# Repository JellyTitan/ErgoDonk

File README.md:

# ErgoDonk v0.9
ErgoDox variant that uses standard 100% SA keycaps, Blackpill MCU and an FDM printed case. 

[keyboard layout editor](http://www.keyboard-layout-editor.com/#/gists/ac776db3b0deef94de51943c384cfdfc)

## Build Log
Experiments to date:
* Prototype initially built with Blackpill MCU. Works well.
* Refactored to use LED
* Refactored to use ProMicro
* Refactored to use Pico 2040
* Prototype sent out for production 7-26-2023

### Lessons learned from the ds simple prototype (todo)
* Fix the stabilizers. Two screw-in PCB stabalizers won't fit next to each other on the thumb cluster - try the plate mount stabs instead.

* Take a closer look at routing by the rotary encoders - may be a short
* The DS version is charged as two keyboards by JLCPCB - compare pricing for building as two seperate halves.
* The RH Trackball has 2 separate pcbs. Top one sent out for prototype, bottom needs to be made.

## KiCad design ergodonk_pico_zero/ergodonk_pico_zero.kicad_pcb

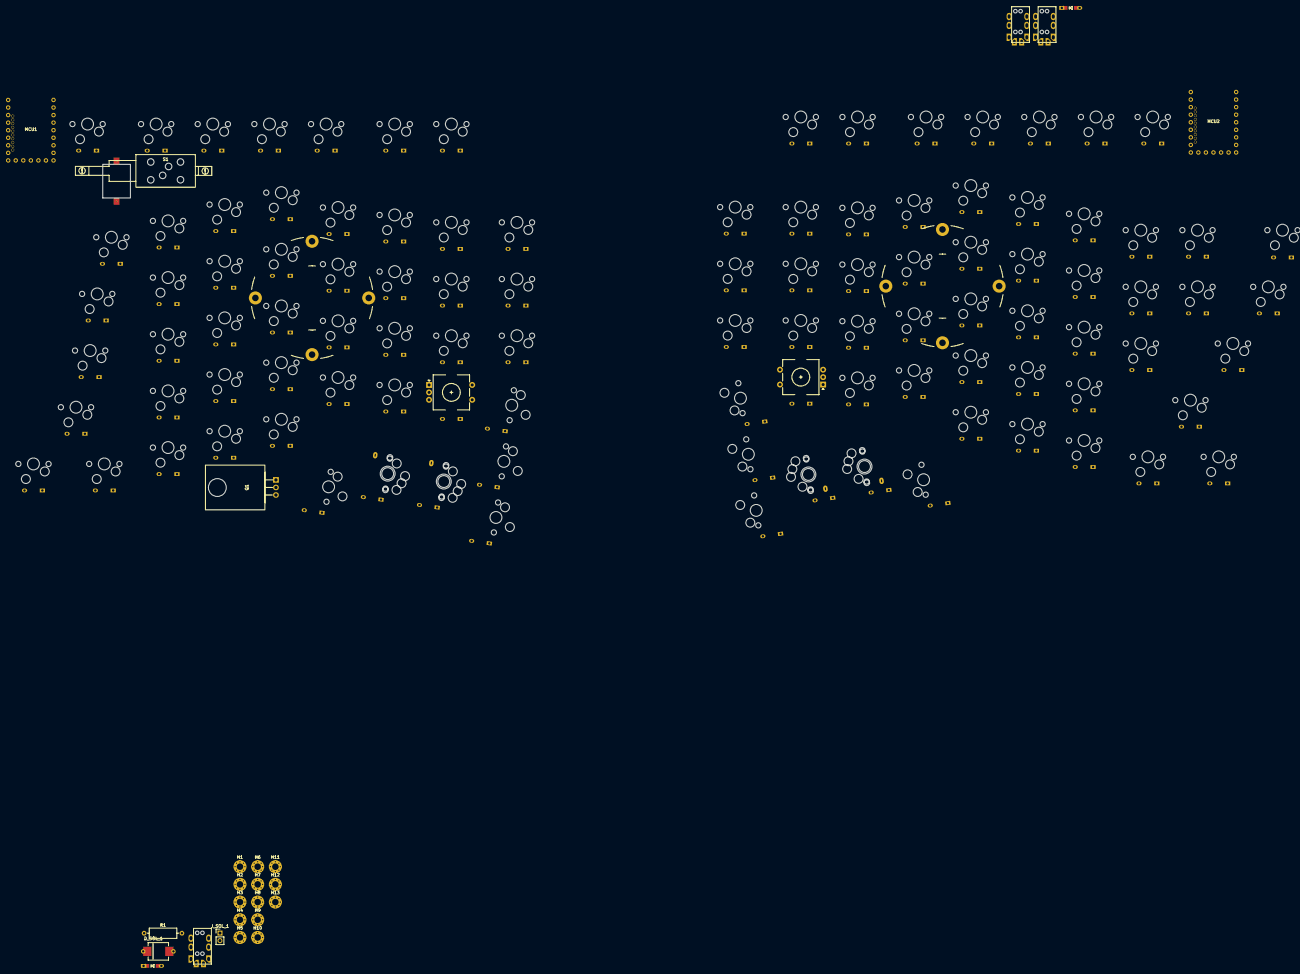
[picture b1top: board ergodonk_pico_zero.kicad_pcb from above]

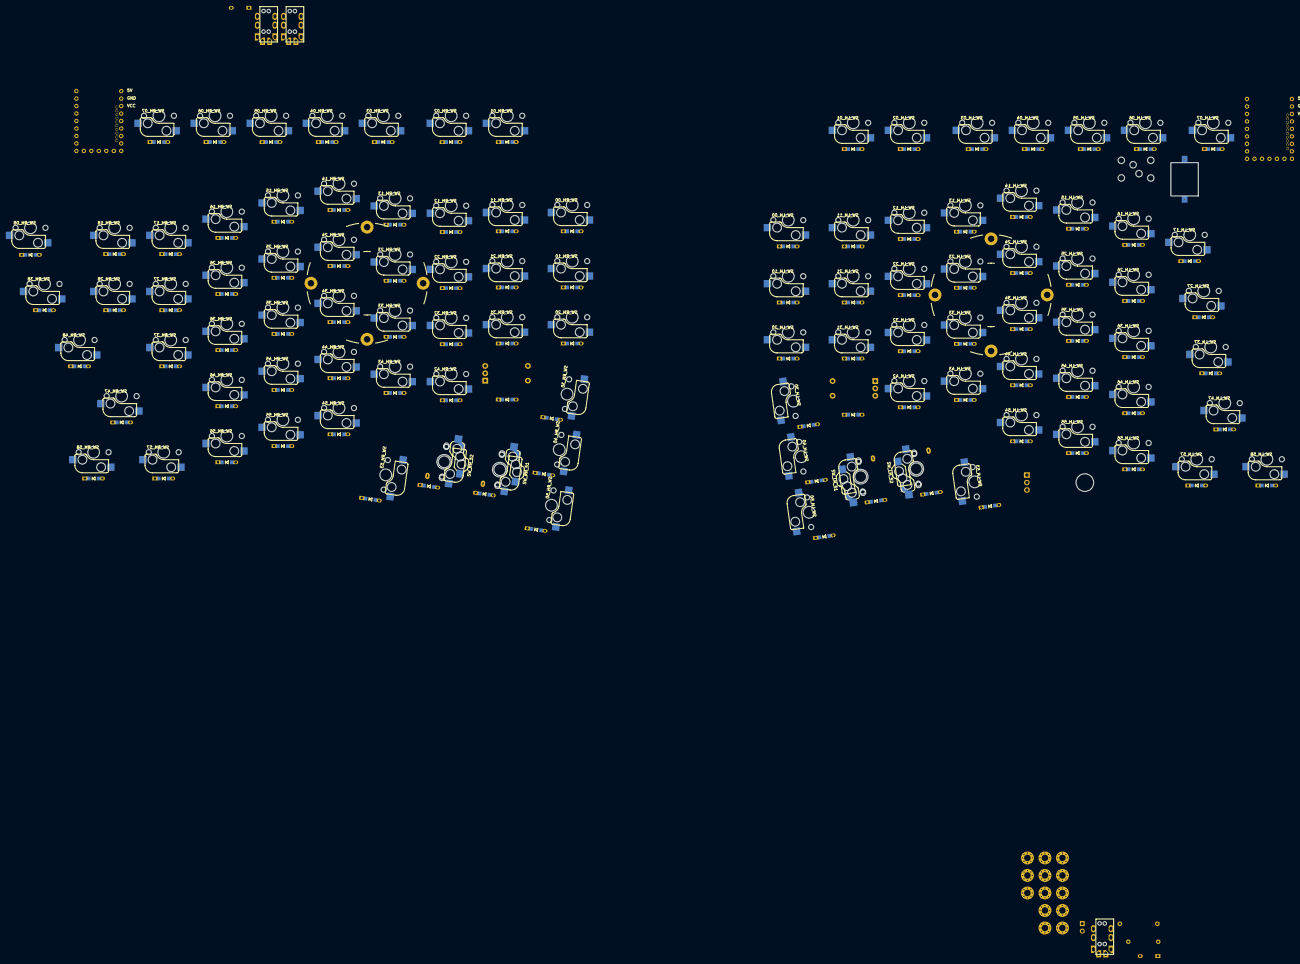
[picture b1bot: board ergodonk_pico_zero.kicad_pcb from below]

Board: 2 copper layers, 234 parts (204 on the bottom side), 143 nets, no tracks yet.

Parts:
D1, D102: D; D3_TH_SMD_v2
D_LH_00, D_LH_01, D_LH_02, D_LH_03, D_LH_04, D_LH_05, D_LH_06, D_LH_07, D_LH_10, D_LH_11, D_LH_12, D_LH_13, D_LH_14, D_LH_15, D_LH_16, D_LH_17, D_LH_20, D_LH_21, D_LH_22, D_LH_23, D_LH_24, D_LH_25, D_LH_26, D_LH_27, D_LH_30, D_LH_31, D_LH_32, D_LH_33, D_LH_34, D_LH_35, D_LH_36, D_LH_37, D_LH_40, D_LH_41, D_LH_42, D_LH_43, D_LH_44, D_LH_45, D_LH_46, D_LH_47, D_LH_50, D_LH_51, D_LH_52, D_LH_53, D_LH_54, D_LH_55, D_LH_56, D_LH_57, D_LH_58: D; D3_TH_SMD_v2
D_RH_00, D_RH_01, D_RH_02, D_RH_03, D_RH_04, D_RH_05, D_RH_06, D_RH_07, D_RH_08, D_RH_10, D_RH_11, D_RH_12, D_RH_13, D_RH_14, D_RH_15, D_RH_16, D_RH_17, D_RH_18, D_RH_20, D_RH_21, D_RH_22, D_RH_23, D_RH_24, D_RH_25, D_RH_26, D_RH_27, D_RH_28, D_RH_30, D_RH_31, D_RH_32, D_RH_33, D_RH_34, D_RH_35, D_RH_36, D_RH_37, D_RH_38, D_RH_40, D_RH_41, D_RH_42, D_RH_43, D_RH_44, D_RH_45, D_RH_46, D_RH_47, D_RH_48, D_RH_50, D_RH_51, D_RH_52, D_RH_53, D_RH_54, D_RH_55, D_RH_56, D_RH_57, D_RH_58: D; D3_TH_SMD_v2
D_SOL_1: MUR340S; MUR340S_IN4001_TH_HYBRID
H1, H2, H3, H4, H5, H6, H7, H8, H9, H10, H11, H12, H13: MountingHole; MountingHole_2.2mm_M2_Pad_Via
H14, H15: Tenting puck mount; Tenting_Puck.kicad_mod_nocenter
J1, J3, J4: AudioJack4; MJ-4PP-9_CANTOR_KITCHEN_SINK
J_SOL_1: Conn_01x02_Female; PinHeader_1x02_P2.54mm_Vertical
LS1: AST1109MLTRQ_MAL; AST1109MLTRQ
MCU1, MCU2: rp2040-zero; rp2040 Zero DS
Q1: TIP120; Tip 120 with heatsink
R1: 1k; R_Axial_DIN0309_L9.0mm_D3.2mm_P12.70mm_Horizontal
S1: Solenoid; uxcell a14092600ux0438 solenoid
SWLH_ROT1: RotaryEncoder_Switch; RotaryEncoder_EC11_ergodonk_variant
SWRH_ROT1: RotaryEncoder_Switch; RotaryEncoder_EC11_ergodonk_variant
SW_LH_00, SW_LH_01, SW_LH_02, SW_LH_03, SW_LH_04, SW_LH_05, SW_LH_06, SW_LH_07, SW_LH_10, SW_LH_11, SW_LH_12, SW_LH_13, SW_LH_14, SW_LH_15, SW_LH_16, SW_LH_17, SW_LH_20, SW_LH_21, SW_LH_22, SW_LH_23, SW_LH_24, SW_LH_25, SW_LH_26, SW_LH_27, SW_LH_30, SW_LH_31, SW_LH_32, SW_LH_33, SW_LH_34, SW_LH_35, SW_LH_36, SW_LH_37, SW_LH_40, SW_LH_42, SW_LH_43, SW_LH_44, SW_LH_45, SW_LH_46, SW_LH_47, SW_LH_50, SW_LH_53, SW_LH_54, SW_LH_55, SW_LH_56, SW_LH_57, SW_LH_58: SW_PUSH; V2_CherryMX_Hotswap
SW_LH_51, SW_LH_52: SW_PUSH; V2_CherryMX_KailhV2_Hotswap
SW_RH_00, SW_RH_01, SW_RH_02, SW_RH_03, SW_RH_04, SW_RH_05, SW_RH_06, SW_RH_07, SW_RH_08, SW_RH_10, SW_RH_11, SW_RH_12, SW_RH_13, SW_RH_14, SW_RH_15, SW_RH_16, SW_RH_17, SW_RH_18, SW_RH_20, SW_RH_21, SW_RH_22, SW_RH_23, SW_RH_24, SW_RH_25, SW_RH_26, SW_RH_27, SW_RH_28, SW_RH_30, SW_RH_31, SW_RH_32, SW_RH_33, SW_RH_34, SW_RH_35, SW_RH_36, SW_RH_37, SW_RH_38, SW_RH_40, SW_RH_42, SW_RH_43, SW_RH_44, SW_RH_45, SW_RH_46, SW_RH_47, SW_RH_48, SW_RH_50, SW_RH_53, SW_RH_54, SW_RH_55, SW_RH_56, SW_RH_57, SW_RH_58: SW_PUSH; V2_CherryMX_Hotswap
SW_RH_51, SW_RH_52: SW_PUSH; V2_CherryMX_KailhV2_Hotswap

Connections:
+5V: MCU1.23 (5V), MCU2.23 (5V)
GND: LS1.2, MCU1.22 (GND), MCU2.22 (GND), Q1.3 (E), SWLH_ROT1.C, SWRH_ROT1.C
unnamed: D_LH_00.2 (A), SW_LH_00.2
unnamed: D_LH_01.2 (A), SW_LH_01.2
unnamed: D_LH_02.2 (A), SW_LH_02.2
unnamed: D_LH_03.2 (A), SW_LH_03.2
unnamed: D_LH_04.2 (A), SW_LH_04.2
unnamed: D_LH_05.2 (A), SW_LH_05.2
unnamed: D_LH_06.2 (A), SW_LH_06.2
unnamed: D_LH_07.2 (A), SW_LH_07.2
unnamed: D_LH_10.2 (A), SW_LH_10.2
unnamed: D_LH_11.2 (A), SW_LH_11.2
unnamed: D_LH_12.2 (A), SW_LH_12.2
unnamed: D_LH_13.2 (A), SW_LH_13.2
unnamed: D_LH_14.2 (A), SW_LH_14.2
unnamed: D_LH_15.2 (A), SW_LH_15.2
unnamed: D_LH_16.2 (A), SW_LH_16.2
unnamed: D_LH_17.2 (A), SW_LH_17.2
unnamed: D_LH_20.2 (A), SW_LH_20.2
unnamed: D_LH_21.2 (A), SW_LH_21.2
unnamed: D_LH_22.2 (A), SW_LH_22.2
unnamed: D_LH_23.2 (A), SW_LH_23.2
unnamed: D_LH_24.2 (A), SW_LH_24.2
unnamed: D_LH_25.2 (A), SW_LH_25.2
unnamed: D_LH_26.2 (A), SW_LH_26.2
unnamed: D_LH_27.2 (A), SW_LH_27.2
unnamed: D_LH_30.2 (A), SW_LH_30.2
unnamed: D_LH_31.2 (A), SW_LH_31.2
unnamed: D_LH_32.2 (A), SW_LH_32.2
unnamed: D_LH_33.2 (A), SW_LH_33.2
unnamed: D_LH_34.2 (A), SW_LH_34.2
unnamed: D_LH_35.2 (A), SW_LH_35.2
unnamed: D_LH_36.2 (A), SW_LH_36.2
unnamed: D_LH_37.2 (A), SW_LH_37.2
unnamed: D_LH_40.2 (A), SW_LH_40.2
unnamed: D_LH_42.2 (A), SW_LH_42.2
unnamed: D_LH_43.2 (A), SW_LH_43.2
unnamed: D_LH_44.2 (A), SW_LH_44.2
unnamed: D_LH_45.2 (A), SW_LH_45.2
unnamed: D_LH_46.2 (A), SW_LH_46.2
unnamed: D_LH_47.2 (A), SW_LH_47.2
unnamed: D_LH_50.2 (A), SW_LH_50.2
unnamed: D_LH_51.2 (A), SW_LH_51.2
unnamed: D_LH_52.2 (A), SW_LH_52.2
unnamed: D_LH_53.2 (A), SW_LH_53.2
unnamed: D_LH_54.2 (A), SW_LH_54.2
unnamed: D_LH_55.2 (A), SW_LH_55.2
unnamed: D_LH_56.2 (A), SW_LH_56.2
unnamed: D_LH_57.2 (A), SW_LH_57.2
unnamed: D_LH_58.2 (A), SW_LH_58.2
unnamed: D_RH_00.2 (A), SW_RH_00.2
unnamed: D_RH_01.2 (A), SW_RH_01.2
unnamed: D_RH_02.2 (A), SW_RH_02.2
unnamed: D_RH_03.2 (A), SW_RH_03.2
unnamed: D_RH_04.2 (A), SW_RH_04.2
unnamed: D_RH_05.2 (A), SW_RH_05.2
unnamed: D_RH_06.2 (A), SW_RH_06.2
unnamed: D_RH_07.2 (A), SW_RH_07.2
unnamed: D_RH_08.2 (A), SW_RH_08.2
unnamed: D_RH_10.2 (A), SW_RH_10.2
unnamed: D_RH_11.2 (A), SW_RH_11.2
unnamed: D_RH_12.2 (A), SW_RH_12.2
unnamed: D_RH_13.2 (A), SW_RH_13.2
unnamed: D_RH_14.2 (A), SW_RH_14.2
unnamed: D_RH_15.2 (A), SW_RH_15.2
unnamed: D_RH_16.2 (A), SW_RH_16.2
unnamed: D_RH_17.2 (A), SW_RH_17.2
unnamed: D_RH_18.2 (A), SW_RH_18.2
unnamed: D_RH_20.2 (A), SW_RH_20.2
unnamed: D_RH_21.2 (A), SW_RH_21.2
unnamed: D_RH_22.2 (A), SW_RH_22.2
unnamed: D_RH_23.2 (A), SW_RH_23.2
unnamed: D_RH_24.2 (A), SW_RH_24.2
unnamed: D_RH_25.2 (A), SW_RH_25.2
unnamed: D_RH_26.2 (A), SW_RH_26.2
unnamed: D_RH_27.2 (A), SW_RH_27.2
unnamed: D_RH_28.2 (A), SW_RH_28.2
unnamed: D_RH_30.2 (A), SW_RH_30.2
unnamed: D_RH_31.2 (A), SW_RH_31.2
unnamed: D_RH_32.2 (A), SW_RH_32.2
unnamed: D_RH_33.2 (A), SW_RH_33.2
unnamed: D_RH_34.2 (A), SW_RH_34.2
unnamed: D_RH_35.2 (A), SW_RH_35.2
unnamed: D_RH_36.2 (A), SW_RH_36.2
unnamed: D_RH_37.2 (A), SW_RH_37.2
unnamed: D_RH_38.2 (A), SW_RH_38.2
unnamed: D_RH_40.2 (A), SW_RH_40.2
unnamed: D_RH_42.2 (A), SW_RH_42.2
unnamed: D_RH_43.2 (A), SW_RH_43.2
unnamed: D_RH_44.2 (A), SW_RH_44.2
unnamed: D_RH_45.2 (A), SW_RH_45.2
unnamed: D_RH_46.2 (A), SW_RH_46.2
unnamed: D_RH_47.2 (A), SW_RH_47.2
unnamed: D_RH_48.2 (A), SW_RH_48.2
unnamed: D_RH_50.2 (A), SW_RH_50.2
unnamed: D_RH_51.2 (A), SW_RH_51.2
unnamed: D_RH_52.2 (A), SW_RH_52.2
unnamed: D_RH_53.2 (A), SW_RH_53.2
unnamed: D_RH_54.2 (A), SW_RH_54.2
unnamed: D_RH_55.2 (A), SW_RH_55.2
unnamed: D_RH_56.2 (A), SW_RH_56.2
unnamed: D_RH_57.2 (A), SW_RH_57.2
unnamed: D_RH_58.2 (A), SW_RH_58.2
unnamed: D_SOL_1.A, J_SOL_1.1, Q1.2 (C)
unnamed: Q1.1 (B), R1.1
SOLENOID_CONTROL: MCU1.20 (29), R1.2
SW_LH_41_A: MCU1.4 (3), SWLH_ROT1.S1, SW_LH_01.1, SW_LH_11.1, SW_LH_21.1, SW_LH_31.1, SW_LH_51.1
SW_LH_41_B: D_LH_41.2 (A), SWLH_ROT1.S2
SW_RH_41_A: MCU2.4 (3), SWRH_ROT1.S1, SW_RH_01.1, SW_RH_11.1, SW_RH_21.1, SW_RH_31.1, SW_RH_51.1
SW_RH_41_B: D_RH_41.2 (A), SWRH_ROT1.S2
VCC: D1.1 (K), D102.1 (K), D_SOL_1.C, J_SOL_1.2, MCU1.21 (3V3), MCU2.21 (3V3)
col0: MCU1.3 (2), SW_LH_00.1, SW_LH_10.1, SW_LH_20.1, SW_LH_30.1, SW_LH_40.1, SW_LH_50.1
col0_rh: MCU2.3 (2), SW_RH_00.1, SW_RH_10.1, SW_RH_20.1, SW_RH_30.1, SW_RH_40.1, SW_RH_50.1
col2: MCU1.5 (4), SW_LH_02.1, SW_LH_12.1, SW_LH_22.1, SW_LH_32.1, SW_LH_42.1, SW_LH_52.1
col2_rh: MCU2.5 (4), SW_RH_02.1, SW_RH_12.1, SW_RH_22.1, SW_RH_32.1, SW_RH_42.1, SW_RH_52.1
col3: MCU1.6 (5), SW_LH_03.1, SW_LH_13.1, SW_LH_23.1, SW_LH_33.1, SW_LH_43.1, SW_LH_53.1
col3_rh: MCU2.6 (5), SW_RH_03.1, SW_RH_13.1, SW_RH_23.1, SW_RH_33.1, SW_RH_43.1, SW_RH_53.1
col4: MCU1.7 (6), SW_LH_04.1, SW_LH_14.1, SW_LH_24.1, SW_LH_34.1, SW_LH_44.1, SW_LH_54.1
col4_rh: MCU2.7 (6), SW_RH_04.1, SW_RH_14.1, SW_RH_24.1, SW_RH_34.1, SW_RH_44.1, SW_RH_54.1
col5: MCU1.8 (7), SW_LH_05.1, SW_LH_15.1, SW_LH_25.1, SW_LH_35.1, SW_LH_45.1, SW_LH_55.1
col5_rh: MCU2.8 (7), SW_RH_05.1, SW_RH_15.1, SW_RH_25.1, SW_RH_35.1, SW_RH_45.1, SW_RH_55.1
col6: MCU1.9 (8), SW_LH_06.1, SW_LH_16.1, SW_LH_26.1, SW_LH_36.1, SW_LH_46.1, SW_LH_56.1
col6_rh: MCU2.9 (8), SW_RH_06.1, SW_RH_16.1, SW_RH_26.1, SW_RH_36.1, SW_RH_46.1, SW_RH_56.1
col7: MCU1.13 (12), SW_LH_07.1, SW_LH_17.1, SW_LH_27.1, SW_LH_37.1, SW_LH_47.1, SW_LH_57.1
col7_rh: MCU2.13 (12), SW_RH_07.1, SW_RH_17.1, SW_RH_27.1, SW_RH_37.1, SW_RH_47.1, SW_RH_57.1
col8: MCU1.12 (11), SW_LH_58.1
col8_rh: MCU2.12 (11), SW_RH_08.1, SW_RH_18.1, SW_RH_28.1, SW_RH_38.1, SW_RH_48.1, SW_RH_58.1
data1RX: MCU1.2 (1), MCU2.2 (1)
data1TX: MCU1.1 (0), MCU2.1 (0)
encA_rh: MCU2.11 (10), SWRH_ROT1.A
encB_rh: MCU2.10 (9), SWRH_ROT1.B
row0: D_LH_00.1 (K), D_LH_01.1 (K), D_LH_02.1 (K), D_LH_03.1 (K), D_LH_04.1 (K), D_LH_05.1 (K), D_LH_06.1 (K), D_LH_07.1 (K), MCU1.19 (28)
row0_rh: D_RH_00.1 (K), D_RH_01.1 (K), D_RH_02.1 (K), D_RH_03.1 (K), D_RH_04.1 (K), D_RH_05.1 (K), D_RH_06.1 (K), D_RH_07.1 (K), D_RH_08.1 (K), MCU2.19 (28)
row1: D_LH_10.1 (K), D_LH_11.1 (K), D_LH_12.1 (K), D_LH_13.1 (K), D_LH_14.1 (K), D_LH_15.1 (K), D_LH_16.1 (K), D_LH_17.1 (K), MCU1.18 (27)
row1_rh: D_RH_10.1 (K), D_RH_11.1 (K), D_RH_12.1 (K), D_RH_13.1 (K), D_RH_14.1 (K), D_RH_15.1 (K), D_RH_16.1 (K), D_RH_17.1 (K), D_RH_18.1 (K), MCU2.18 (27)
row2: D_LH_20.1 (K), D_LH_21.1 (K), D_LH_22.1 (K), D_LH_23.1 (K), D_LH_24.1 (K), D_LH_25.1 (K), D_LH_26.1 (K), D_LH_27.1 (K), MCU1.17 (26)
row2_rh: D_RH_20.1 (K), D_RH_21.1 (K), D_RH_22.1 (K), D_RH_23.1 (K), D_RH_24.1 (K), D_RH_25.1 (K), D_RH_26.1 (K), D_RH_27.1 (K), D_RH_28.1 (K), MCU2.17 (26)
row3: D_LH_30.1 (K), D_LH_31.1 (K), D_LH_32.1 (K), D_LH_33.1 (K), D_LH_34.1 (K), D_LH_35.1 (K), D_LH_36.1 (K), D_LH_37.1 (K), MCU1.16 (15)
row3_rh: D_RH_30.1 (K), D_RH_31.1 (K), D_RH_32.1 (K), D_RH_33.1 (K), D_RH_34.1 (K), D_RH_35.1 (K), D_RH_36.1 (K), D_RH_37.1 (K), D_RH_38.1 (K), MCU2.16 (15)
row4: D_LH_40.1 (K), D_LH_41.1 (K), D_LH_42.1 (K), D_LH_43.1 (K), D_LH_44.1 (K), D_LH_45.1 (K), D_LH_46.1 (K), D_LH_47.1 (K), MCU1.15 (14)
row4_rh: D_RH_40.1 (K), D_RH_41.1 (K), D_RH_42.1 (K), D_RH_43.1 (K), D_RH_44.1 (K), D_RH_45.1 (K), D_RH_46.1 (K), D_RH_47.1 (K), D_RH_48.1 (K), MCU2.15 (14)
row5: D_LH_50.1 (K), D_LH_51.1 (K), D_LH_52.1 (K), D_LH_53.1 (K), D_LH_54.1 (K), D_LH_55.1 (K), D_LH_56.1 (K), D_LH_57.1 (K), D_LH_58.1 (K), MCU1.14 (13)
row5_rh: D_RH_50.1 (K), D_RH_51.1 (K), D_RH_52.1 (K), D_RH_53.1 (K), D_RH_54.1 (K), D_RH_55.1 (K), D_RH_56.1 (K), D_RH_57.1 (K), D_RH_58.1 (K), MCU2.14 (13)

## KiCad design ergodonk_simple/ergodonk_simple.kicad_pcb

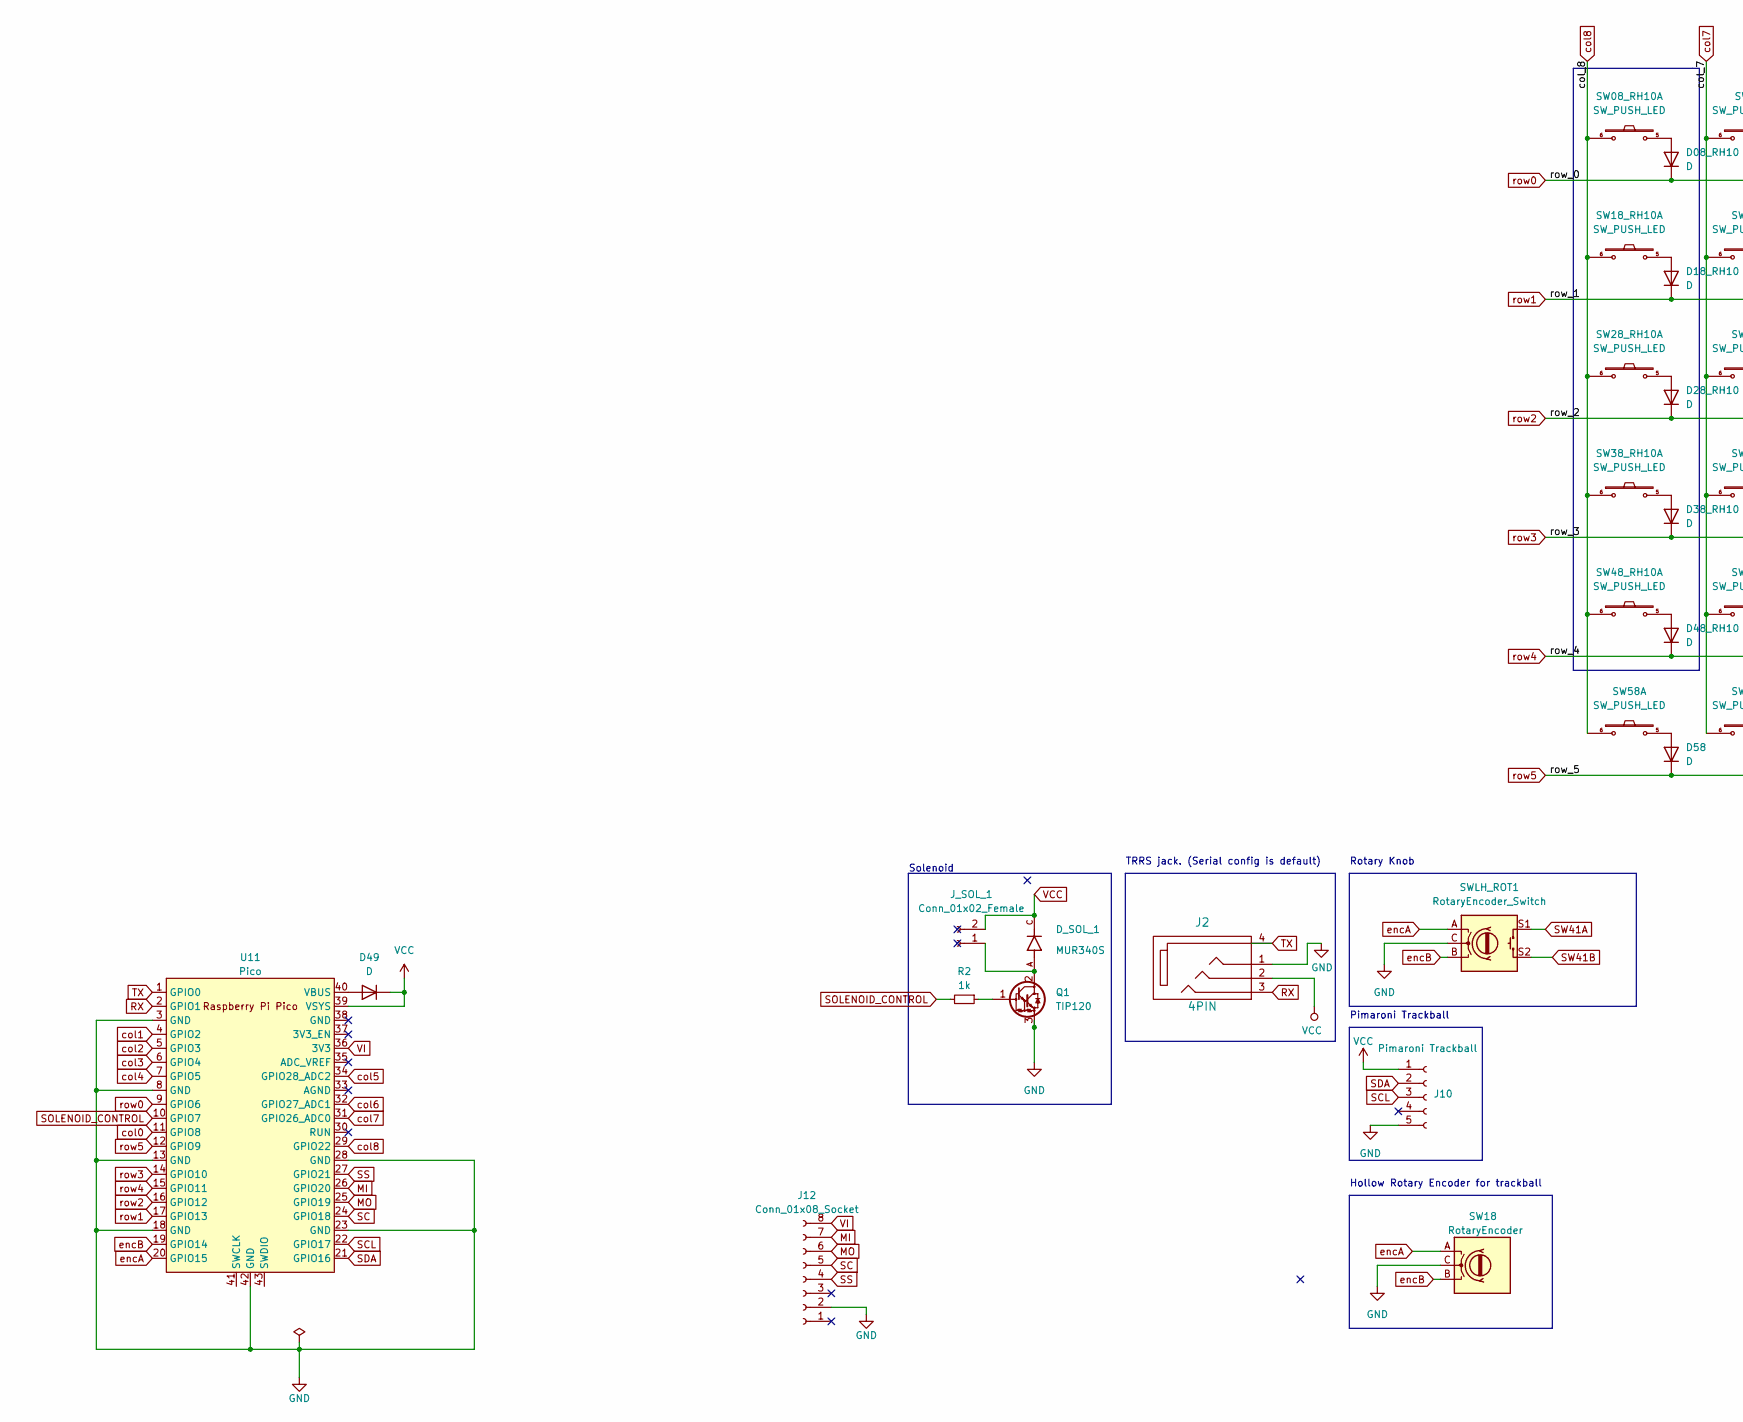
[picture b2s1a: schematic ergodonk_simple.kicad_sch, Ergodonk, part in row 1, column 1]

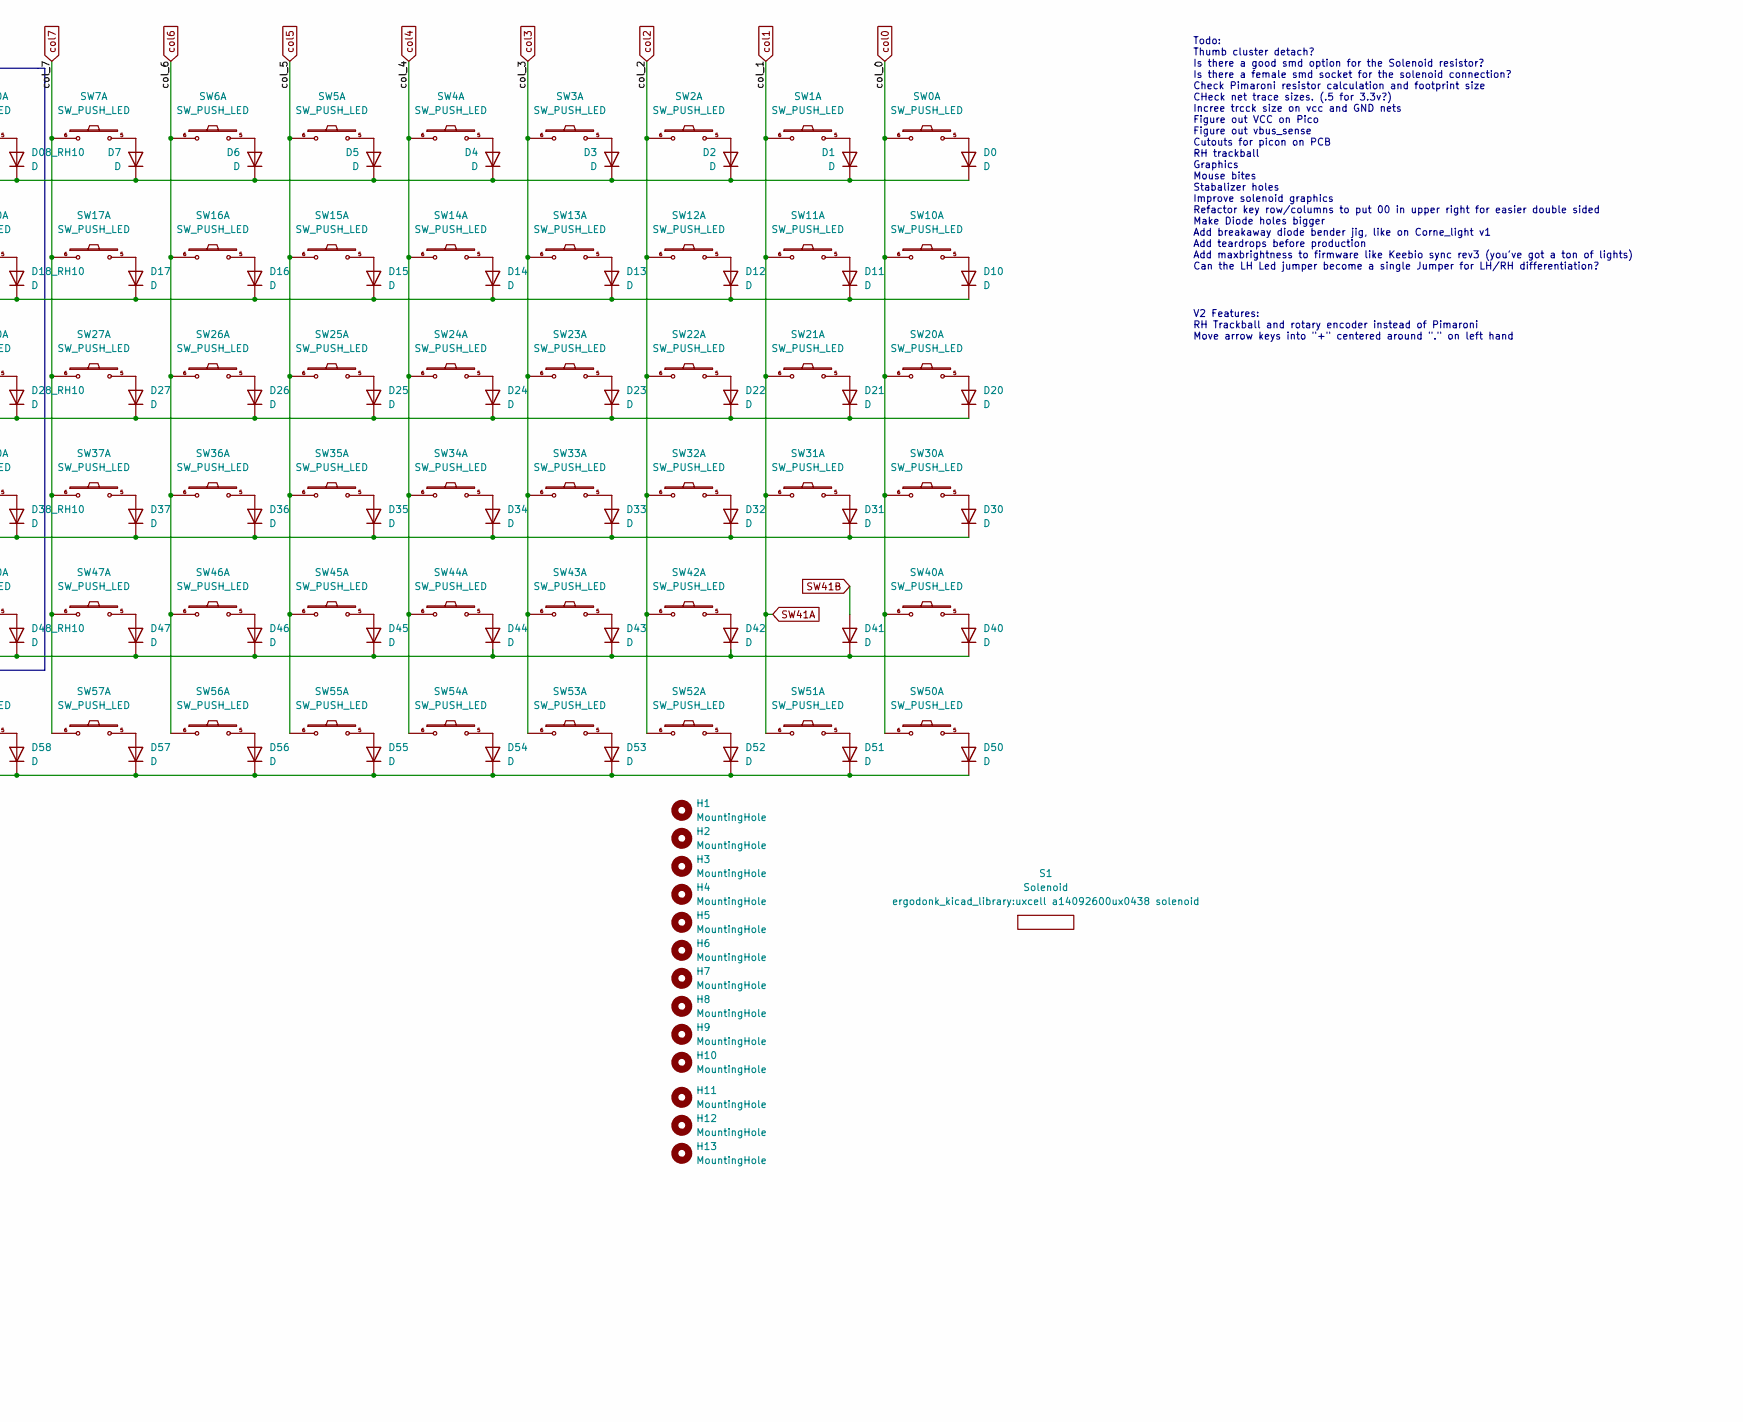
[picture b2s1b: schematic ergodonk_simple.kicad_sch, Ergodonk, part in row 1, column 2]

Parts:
D0, D1, D2, D3, D4, D5, D6, D7, D08_RH10, D10, D11, D12, D13, D14, D15, D16, D17, D18_RH10, D20, D21, D22, D23, D24, D25, D26, D27, D28_RH10, D30, D31, D32, D33, D34, D35, D36, D37, D38_RH10, D40, D41, D42, D43, D44, D45, D46, D47, D48_RH10, D50, D51, D52, D53, D54, D55, D56, D57, D58: D; D_SOD-123_DO-35_Hybrid_DoubleSided
D49: D; D3_TH_SMD_v2
D_SOL_1: MUR340S; MUR340S_IN4001_TH_HYBRID; PARTREV L2102
H1, H2, H3, H4, H5, H6, H7, H8, H9, H10, H11, H12, H13: MountingHole; Hole from sofle for M2 posts gold rimmer
J2: 4PIN; MJ-4PP-9_CANTOR_KITCHEN_SINK
J10: Pimaroni Trackball; pimoroni_trackball_no_cutout
J12: Conn_01x08_Socket; PinHeader_1x08_P2.54mm_Vertical
J_SOL_1: Conn_01x02_Female; PinHeader_1x02_P2.54mm_Vertical
Q1: TIP120; TO-220-3_Horizontal_TabDown
R2: 1k; R_Axial_DIN0309_L9.0mm_D3.2mm_P12.70mm_Horizontal
S1: Solenoid; uxcell a14092600ux0438 solenoid
SW0, SW1, SW2, SW3, SW4, SW5, SW6, SW7, SW10, SW11, SW12, SW13, SW14, SW15, SW16, SW17, SW20, SW21, SW22, SW23, SW24, SW25, SW26, SW30, SW31, SW32, SW33, SW34, SW35, SW36, SW40, SW42, SW43, SW44, SW45, SW46, SW50, SW51, SW52, SW53, SW54, SW55, SW56, SW57, SW58: SW_PUSH_LED; Cherry_MX_DS_Hotswap_1U_sofle3b v3
SW08_RH10: SW_PUSH_LED; V2_CherryMX_DoubleSided_Hotswap_miniE_2u_RH_ONLY
SW18: RotaryEncoder; Bourns Hollow Encoder V1
SW18_RH10, SW38_RH10: SW_PUSH_LED; Cherry_MX_DS_Hotswap_1U_oneside
SW27: SW_PUSH_LED; V2_CherryMX_DoubleSided_Hotswap_miniE_1.5u_LH_1u_RH
SW28_RH10: SW_PUSH_LED; V2_CherryMX_DoubleSided_Hotswap_miniE_1.5u_RH_ONLY
SW37: SW_PUSH_LED; V2_CherryMX_DoubleSided_Hotswap_miniE_1.75u_LH_1u_RH
SW47: SW_PUSH_LED; V2_CherryMX_DoubleSided_Hotswap_miniE_2.25u_LH_2.75u_RH
SW48_RH10: SW_PUSH_LED; V2_CherryMX_DoubleSided_Hotswap_miniE_2.25u_RH_ONLY
SWLH_ROT1: RotaryEncoder_Switch; RotaryEncoder_EC11_ergodonk_variant
U11: Pico; RPi_Pico_SMD_TH_DS_Simple_v1

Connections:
GND: J10.5, J12.2, Q1.3 (E), SW18.C, SWLH_ROT1.C, U11.3 (GND), U11.8 (GND), U11.13 (GND), U11.18 (GND), U11.23 (GND), U11.28 (GND), U11.42 (GND); also elsewhere on the board
MI: J12.7, U11.26 (GPIO20)
MO: J12.6, U11.25 (GPIO19)
unnamed: D0.2 (A), SW0.5
unnamed: D1.2 (A), SW1.5
unnamed: D2.2 (A), SW2.5
unnamed: D3.2 (A), SW3.5
unnamed: D4.2 (A), SW4.5
unnamed: D5.2 (A), SW5.5
unnamed: D6.2 (A), SW6.5
unnamed: D7.2 (A), SW7.5
unnamed: D08_RH10.2 (A), SW08_RH10.5
unnamed: D10.2 (A), SW10.5
unnamed: D11.2 (A), SW11.5
unnamed: D12.2 (A), SW12.5
unnamed: D13.2 (A), SW13.5
unnamed: D14.2 (A), SW14.5
unnamed: D15.2 (A), SW15.5
unnamed: D16.2 (A), SW16.5
unnamed: D17.2 (A), SW17.5
unnamed 20: U11.40 (VBUS); also elsewhere on the board
unnamed: D18_RH10.2 (A), SW18_RH10.5
unnamed: D20.2 (A), SW20.5
unnamed: D21.2 (A), SW21.5
unnamed: D22.2 (A), SW22.5
unnamed: D23.2 (A), SW23.5
unnamed: D24.2 (A), SW24.5
unnamed: D25.2 (A), SW25.5
unnamed: D26.2 (A), SW26.5
unnamed: D27.2 (A), SW27.5
unnamed: D28_RH10.2 (A), SW28_RH10.5
unnamed: D30.2 (A), SW30.5
unnamed: D31.2 (A), SW31.5
unnamed: D32.2 (A), SW32.5
unnamed: D33.2 (A), SW33.5
unnamed: D34.2 (A), SW34.5
unnamed: D35.2 (A), SW35.5
unnamed: D36.2 (A), SW36.5
unnamed: D37.2 (A), SW37.5
unnamed: D38_RH10.2 (A), SW38_RH10.5
unnamed: D40.2 (A), SW40.5
unnamed: D42.2 (A), SW42.5
unnamed: D43.2 (A), SW43.5
unnamed: D44.2 (A), SW44.5
unnamed: D45.2 (A), SW45.5
unnamed: D46.2 (A), SW46.5
unnamed: D47.2 (A), SW47.5
unnamed: D48_RH10.2 (A), SW48_RH10.5
unnamed: D50.2 (A), SW50.5
unnamed: D51.2 (A), SW51.5
unnamed: D52.2 (A), SW52.5
unnamed: D53.2 (A), SW53.5
unnamed: D54.2 (A), SW54.5
unnamed: D55.2 (A), SW55.5
unnamed: D56.2 (A), SW56.5
unnamed: D57.2 (A), SW57.5
unnamed: D58.2 (A), SW58.5
unnamed: D_SOL_1.A, J_SOL_1.1, Q1.2 (C)
unnamed: Q1.1 (B), R2.1
RX: U11.2 (GPIO1); also elsewhere on the board
SC: J12.5, U11.24 (GPIO18)
SCL: J10.3, U11.22 (GPIO17)
SDA: J10.2, U11.21 (GPIO16)
SOLENOID_CONTROL: R2.2, U11.10 (GPIO7)
SS: J12.4, U11.27 (GPIO21)
SW41A: SW1.6, SW11.6, SW21.6, SW31.6, SW51.6, SWLH_ROT1.S1, U11.4 (GPIO2)
SW41B: D41.2 (A), SWLH_ROT1.S2
TX: U11.1 (GPIO0); also elsewhere on the board
VCC: D_SOL_1.C, J10.1, J_SOL_1.2, U11.39 (VSYS); also elsewhere on the board
VI: J12.8, U11.36 (3V3)
col0: SW0.6, SW10.6, SW20.6, SW30.6, SW40.6, SW50.6, U11.11 (GPIO8)
col2: SW2.6, SW12.6, SW22.6, SW32.6, SW42.6, SW52.6, U11.5 (GPIO3)
col3: SW3.6, SW13.6, SW23.6, SW33.6, SW43.6, SW53.6, U11.6 (GPIO4)
col4: SW4.6, SW14.6, SW24.6, SW34.6, SW44.6, SW54.6, U11.7 (GPIO5)
col5: SW5.6, SW15.6, SW25.6, SW35.6, SW45.6, SW55.6, U11.34 (GPIO28_ADC2)
col6: SW6.6, SW16.6, SW26.6, SW36.6, SW46.6, SW56.6, U11.32 (GPIO27_ADC1)
col7: SW7.6, SW17.6, SW27.6, SW37.6, SW47.6, SW57.6, U11.31 (GPIO26_ADC0)
col8: SW08_RH10.6, SW18_RH10.6, SW28_RH10.6, SW38_RH10.6, SW48_RH10.6, SW58.6, U11.29 (GPIO22)
encA: SW18.A, SWLH_ROT1.A, U11.20 (GPIO15)
encB: SW18.B, SWLH_ROT1.B, U11.19 (GPIO14)
row0: D0.1 (K), D1.1 (K), D2.1 (K), D3.1 (K), D4.1 (K), D5.1 (K), D6.1 (K), D7.1 (K), D08_RH10.1 (K), U11.9 (GPIO6)
row1: D10.1 (K), D11.1 (K), D12.1 (K), D13.1 (K), D14.1 (K), D15.1 (K), D16.1 (K), D17.1 (K), D18_RH10.1 (K), U11.17 (GPIO13)
row2: D20.1 (K), D21.1 (K), D22.1 (K), D23.1 (K), D24.1 (K), D25.1 (K), D26.1 (K), D27.1 (K), D28_RH10.1 (K), U11.16 (GPIO12)
row3: D30.1 (K), D31.1 (K), D32.1 (K), D33.1 (K), D34.1 (K), D35.1 (K), D36.1 (K), D37.1 (K), D38_RH10.1 (K), U11.14 (GPIO10)
row4: D40.1 (K), D41.1 (K), D42.1 (K), D43.1 (K), D44.1 (K), D45.1 (K), D46.1 (K), D47.1 (K), D48_RH10.1 (K), U11.15 (GPIO11)
row5: D50.1 (K), D51.1 (K), D52.1 (K), D53.1 (K), D54.1 (K), D55.1 (K), D56.1 (K), D57.1 (K), D58.1 (K), U11.12 (GPIO9)

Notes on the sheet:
Todo: Thumb cluster detach? Is there a good smd option for the Solenoid resistor? Is there a female smd socket for the solenoid connection? Check Pimaroni resistor calculation and footprint size CHeck net trace sizes. (.5 for 3.3v?) Incree trcck size on vcc and GND nets Figure out VCC on Pico Figur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
Pimaroni Trackball
Solenoid
V2 Features: RH Trackball and rotary encoder instead of Pimaroni Move arrow keys into "+" centered around "." on left hand
TRRS jack. (Serial config is default)
Hollow Rotary Encoder for trackball
Rotary Knob

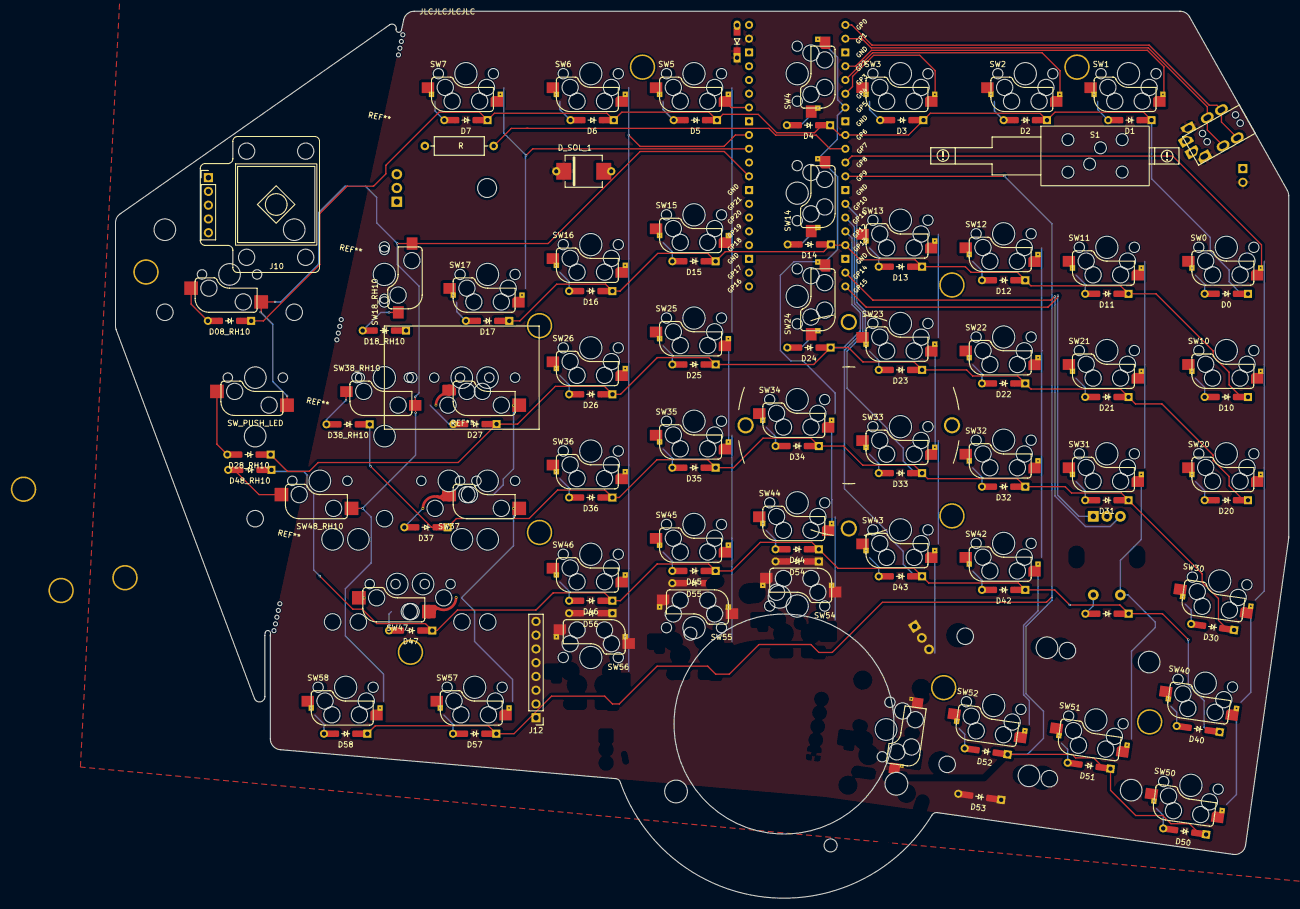
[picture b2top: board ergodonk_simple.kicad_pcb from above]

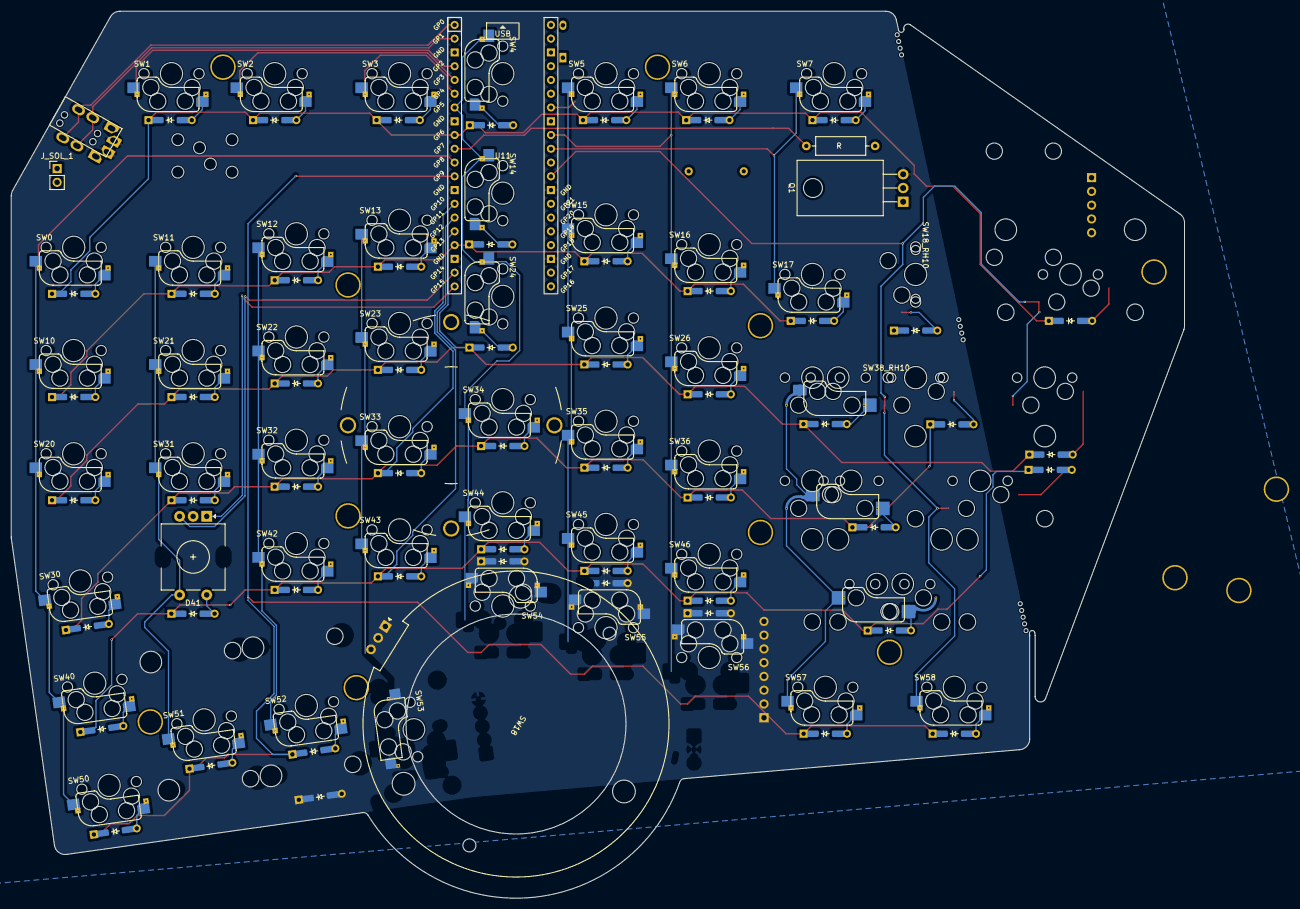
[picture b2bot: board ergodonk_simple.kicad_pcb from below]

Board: 2 copper layers, 216.6 x 163.7 mm, 132 parts (8 on the bottom side), 85 nets.

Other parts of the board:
D18: D; D3_TH_SMD_v2
J11: 4PIN; MJ-4PP-9_CANTOR_KITCHEN_SINK

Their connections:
GND: J11.1; also elsewhere on the board
unnamed 20: D18.2 (A); also elsewhere on the board
RX: J11.3; also elsewhere on the board
TX: J11.4; also elsewhere on the board
VCC: D18.1 (K), J11.2; also elsewhere on the board

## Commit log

2022-11-28 blackpill holder first iteration
2022-11-28 Added thumb
2022-12-08 Updated wiring diagram
2022-12-08 Blackpill holder trrs jack imports
2022-12-08 First draft blackpill wiring diagram
2022-12-08 First draft qmk firmware - communication still needs work
2022-12-14 Updated wiring and firmware
2023-01-09 Solenoid working
2023-01-13 Created PCB (Kicad) Added submodule for Blackpill footprints/symbolsl Added submodule for KBD generic footprints/symbols
2023-01-17 Updated PCB created new footprints based on kbd hybrid TH/SMD diodes Swapped IN4004 for MUR340 in Solenoid Routing and Blackpill placement Added RP2040 symbol/footprint submodule
2023-01-20 LH single side pcb first draft complete sent this version to jlcpcb for prototype production
2023-01-20 Synchronized updated footprints with schematics
2023-01-22 Moved customezed footprints to seperate library and updated schematic association
2023-01-22 Updated kbfirmware wiring layout to gain 1 pin per side
2023-01-22 Added 2u Screw in stabalizers and rerouted wiring
2023-01-24 Wiring cleanup, started adding LEDs
2023-01-24 Updated schematic to V2 wiring - frees up one more pin[B (b3)
2023-01-24 Updated wiring on pcb to v2, ran DRC
2023-01-27 Revised RH wiring diagram and added 3d component models
2023-01-31 Added KiCad libraries for rp2040 pro micro and Sofle Choc
2023-02-01 Created Cherry MX Doublesided mini-e footprint variant and updated schematic
2023-02-01 LED layout before mirroroing
2023-02-01 Button & LED reference sync
2023-02-01 Alpha key LED schematic wiring
2023-02-01 Reveresed nrow/column umbering systme to support double sided
2023-02-02 Right hand added Built new footprints for RH/LH combo keys Added jumpers for optional LEDs"
2023-02-02 Added edgecuts with breakaway right hand
2023-02-04 Added speaker and cleaned up diode placement
2023-02-04 Resolved LED jumper sequence and comments
2023-02-13 First draft of Bourns hollow encoder footprint (sent out for prototype)
2023-02-19 Removed hand indication pin pin and updated footprints
2023-02-20 Updated MX low-profile footrpint and Choc Milk logo
2023-02-26 Increased default net width and removed LED initial jumper
2023-02-26 Switch footprint refactor Hotswop outline replaced and rounded Hotswap pad numbering aligned per side Hotswap pad traces and vias added miniE led footprint with doublesided vias added Schematics upda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
2023-02-27 Played with rp2040 footprints last commit before migration from blackpill 411 to rp2040
2023-02-27 Rewired to 2040 begun Rewired rows and columns Added net names for rows and columns. Removed Key 00 to make room for PI Added OLED Added SDA/SDL breakout for optional Pimoroni
2023-03-01 Updated PCB from schematicatic, diode cleanup
2023-03-01 Simplified LED config to mirror Keebio Sync Rev3
2023-03-01 Removed blackpill from schematic and pcb Updated pico placement Updated outline source for Inkscape regeneration
2023-03-01 Added pimaroni rough symbol
2023-03-07 TRRS cleanup pimironi revision outline rework
2023-03-07 Fixed MUR340 Hybrid footprint Regenerated .dsn for autorouting
2023-03-07 Added zones Wired VCC to VDD for LED Regenerated dsn for autorouting
2023-03-08 Pimoroni footprint cleanup
2023-03-08 Added pico reset button cutout Moved Oled for tilt setup
2023-03-09 Regenerated .dsn with ground and VCC zones
2023-03-10 Added jlc order number location specification
2023-03-10 Revised solenoid footrpints and layout for easier soldering and better fit
2023-03-12 Schematic cleanup for review/assistance
2023-03-13 Rewired to VBus for 5V and updated dsn
2023-03-14 Mounting hole realingmngment for top plate
2023-03-31 Cantor blackpill footprint tweak
2023-03-31 Footprint updates
2023-04-04 General commit before switching machines
2023-04-06 Integrated led footprint from sofle choc_mx Updated schematic from PCB Moved diodes to RH of switches started wiring
2023-04-12 Routing first pass updated keyswitch footprints
2023-04-13 Trace routing
2023-04-13 Cutover to elite-c/elite-pi
2023-04-13 elite-c rewiring continued
2023-04-14 More wiring
2023-04-27 Wiring cleanup for Elite-C variant
2023-05-07 Flipped diodes added tenting puck started rewire with new diode orientation
2023-05-11 Added seperate kicad project for pi pico non double-sided
2023-06-03 Checkpoint commit
2023-06-06 Ergodonk pico schematic update
2023-06-06 Added elite-c variant as subfolder
2023-06-06 Moved F row to accomidate mid board Pico mcu
2023-06-07 Updated pico RH schematics
2023-06-08 Pico schematic switch nubmering changed to row/col intersection
2023-06-09 Pico leds re-added to schemematic PCB rough key layout
2023-06-11 Revised RH row/columns for syntactic sugar
2023-06-11 Thumb rotation diode placement added tenting puck symbols and footprint
2023-06-12 pico diode placement
2023-06-13 Spun out double-sided into corner-oled variant
2023-06-17 Added pmw3360 schematic for pico
2023-06-17 Added offset ds pico experimental footprints
2023-07-13 Added 'simple' variant
2023-07-13 simple variant routing checkpoint commit
2023-07-14 simple variant rh-brh-breakoff outline
2023-07-16 CHeckpoint commit before simple MCU move
2023-07-17 checkpoint
2023-07-18 ergodonk simple lh pico movement abandoned
2023-07-21 pcb simple with encoder checkpoint before outline mod
2023-07-23 Flipped rotary encoder to backside
2023-07-24 Updated thumb stabalizers
2023-07-27 SENT OUT FOR PRODUCTION
2023-07-27 Added underglow to schematic
2023-07-28 Moved trace away from ec11 plated support slot to prevent short
2023-07-29 SENT OUT TRACKBALL PLATE FOR PRODCUTION
2023-08-23 Excluded backup folders from git
2023-11-19 Basic routing on ergodonk pico zero simple
2023-11-20 ergodonk simple zero checkpoint before choc MX switch swap
2023-11-20 Added choc support for ergodonk simple zero
2023-11-20 Most routing complete
